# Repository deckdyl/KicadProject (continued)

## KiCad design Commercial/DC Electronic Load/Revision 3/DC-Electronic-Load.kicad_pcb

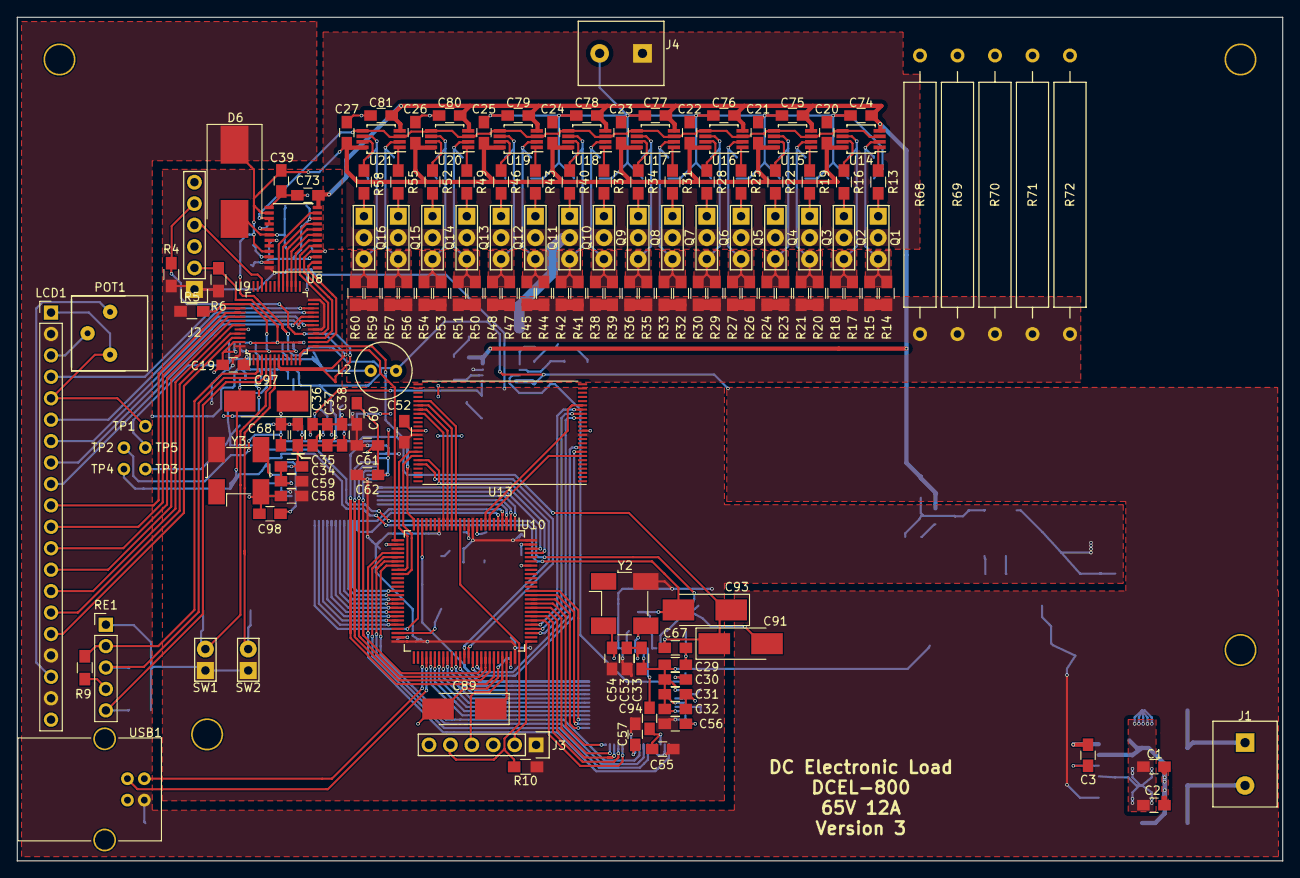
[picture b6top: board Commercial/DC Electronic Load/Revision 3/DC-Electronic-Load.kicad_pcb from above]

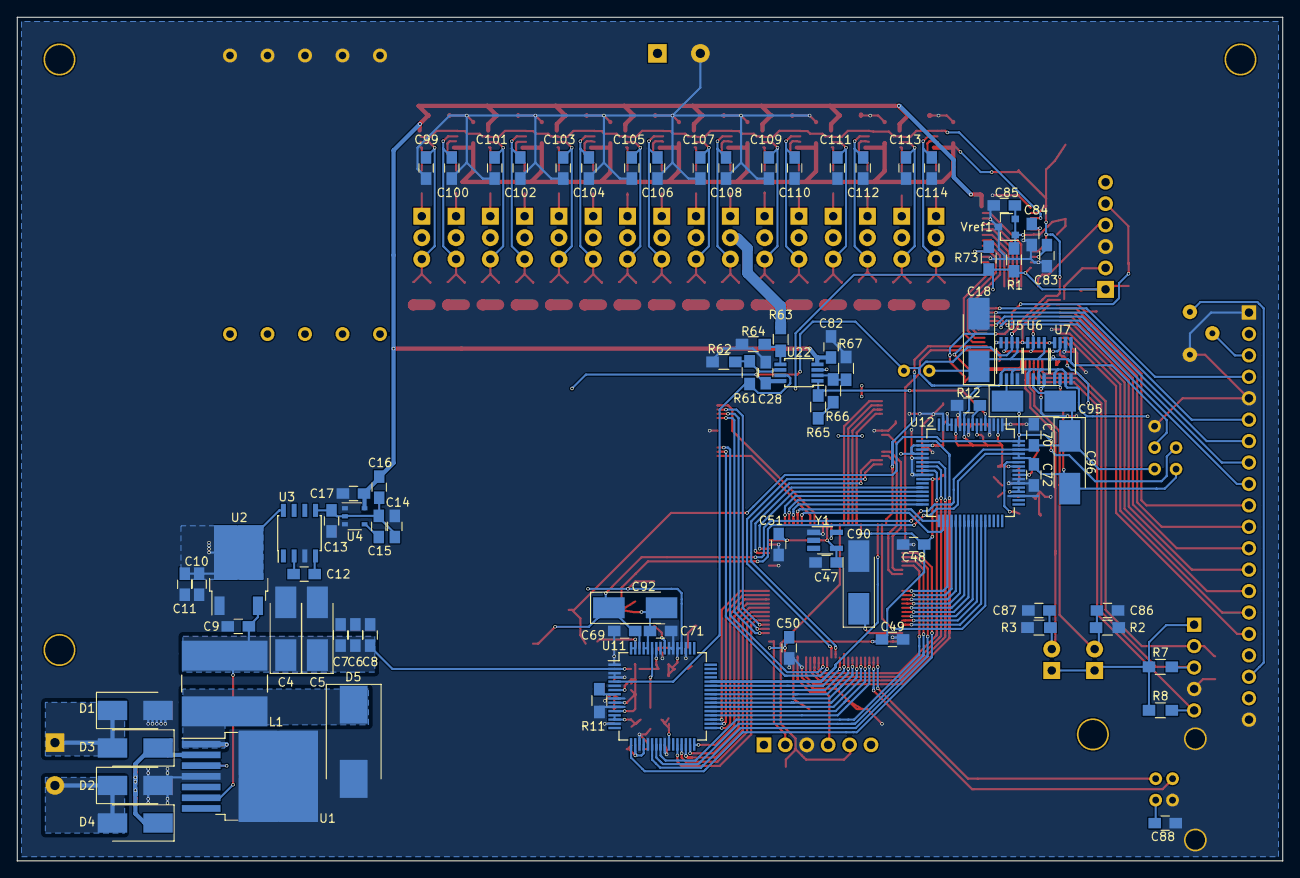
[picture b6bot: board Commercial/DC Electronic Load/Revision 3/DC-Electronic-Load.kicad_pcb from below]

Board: 2 copper layers, 150.0 x 100.0 mm, 241 parts (85 on the bottom side), 181 nets.

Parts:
C1, C2: 22uF; C_0805_HandSoldering
C3, C85, C99, C100, C101, C102, C103, C104, C105, C106, C107, C108, C109, C110, C111, C112, C113, C114: 10nF; C_0805_HandSoldering
C4, C5, C18: 47uF; CP_Tantalum_Case-C_EIA-6032-28_Hand
C6: 4.7uF; C_0805_HandSoldering
C7, C9, C10, C14, C16, C83, C88: 1uF; C_0805_HandSoldering
C8, C11, C15, C17, C19, C20, C21, C22, C23, C24, C25, C26, C27, C28, C29, C30, C31, C32, C33, C34, C35, C36, C37, C38, C39, C47, C48, C49, C50, C51, C52, C53, C54, C55, C56, C57, C58, C59, C60, C61, C62, C67, C68, C69, C70, C71, C72, C73, C74, C75, C76, C77, C78, C79, C80, C81, C82, C86, C87, C94, C98: 100nF; C_0805_HandSoldering
C12, C13: 10uF; C_0805_HandSoldering
C84: 100pF; C_0805_HandSoldering
C89, C90: 2.2uF; CP_Tantalum_Case-C_EIA-6032-28_Hand
C91, C92, C93, C95, C96, C97: 22uF; CP_Tantalum_Case-C_EIA-6032-28_Hand
D1, D2, D3, D4: S2A; D_SMB_Handsoldering
D5, D6: B330; D_SMC_Handsoldering
J1: POWER; Terminal_Block-5mm
J2, J3: ST-Link; Pin_Header_Straight_1x06
J4: Terminal Block; Terminal_Block-5mm
L1: 22uH; Inductor_SMD-9.8X10
L2: 10mH; Inductor_TH-D6.7mm-P3mm
LCD1: LCD_12864; Pin_Header_Straight_1x20_Pitch2.54mm
POT1: 10kΩ; Potentiometer_Bourns_3386
Q1, Q2, Q3, Q4, Q5, Q6, Q7, Q8, Q9, Q10, Q11, Q12, Q13, Q14, Q15, Q16: PSMN5R0-80PS; Pin_Header_Straight_1x03
R1, R13, R16, R19, R22, R25, R28, R31, R34, R37, R40, R43, R46, R49, R52, R55, R58: 100Ω; R_0805_HandSoldering
R2, R3, R4, R10: 10kΩ; R_0805_HandSoldering
R5, R6, R7, R8, R9, R73: 2kΩ; R_0805_HandSoldering
R11, R12: 36kΩ; R_0805_HandSoldering
R14, R15, R17, R18, R20, R21, R23, R24, R26, R27, R29, R30, R32, R33, R35, R36, R38, R39, R41, R42, R44, R45, R47, R48, R50, R51, R53, R54, R56, R57, R59, R60: 2Ω; R_0805_HandSoldering
R61, R62, R64, R65, R66, R67: 26.1kΩ; R_0805_HandSoldering
R63: 750kΩ; R_0805_HandSoldering
R68, R69, R70, R71, R72: 0Ω5; Resistor-5W-PACE05
RE1: Rotary_Encoder; Pin_Header_Straight_1x05_Pitch2.54mm
SW1, SW2: SW_PUSH; Pin_Header_Straight_1x02
TP1, TP2, TP3, TP4, TP5: TEST_1P; Measurement_Point_Round-TH_Small
U1: LM2678-5.0; TO-263-7_TabPin4
U2: NCP1117-3.3; TO-252-2
U3: TC7662; SOIC-8_3.9x4.9mm_Pitch1.27mm
U4: NCP700B-2V8; TSOP-5_1.65x3.05mm_Pitch0.95mm
U5, U6, U7: MAX5215; uMAX
U8: MAX5318; TSSOP-24_4.4x7.8mm_Pitch0.65mm
U9: STM32F373C8T6; LQFP-48_7x7mm_Pitch0.5mm
U10: STM32F446VET6; LQFP-100_14x14mm_Pitch0.5mm
U11, U12: ADS1625/ADS1626; TQFP-64_10x10mm_Pitch0.5mm
U13: TH58BVG3S0; TSOP-I-48_18.4x12mm_Pitch0.5mm
U14, U15, U16, U17, U18, U19, U20, U21, U22: LMP2022; MSOP-8_3x3mm_Pitch0.65mm
USB1: USB_B
Vref1: TL431; SOT-23
Y1: Osc-SMD-SOT23; SOT-23-5_HandSoldering
Y2, Y3: Osc-SMD; Oscillator_SMD_Abracon_ASV-4pin_7.0x5.1mm_HandSoldering

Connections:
12MHz: U10.12, Y1.5
+1V: C71.1, C72.1, C92.2, C93.2, C96.2, C97.2, TP4.1, U7.6, U11.60, U11.61, U12.60, U12.61
+2V5: C69.1, C70.1, C91.2, C92.1, C95.2, C96.1, TP3.1, U6.6, U11.62, U12.62
+3V3: C10.1, C11.1, C47.1, C48.1, C49.1, C50.1, C51.1, C52.1, C53.1, C54.1, C55.1, C56.1, C57.1, C58.1, C59.1, C60.1, C61.1, C62.1, J2.1, J3.1, R1.1, R4.1, R5.1, R6.1, R7.1, R8.1, R10.2, R73.1, RE1.1, SW1.1, SW2.1, U2.2, U3.8, U8.24, U9.17, U9.24, U9.48, U10.11, U10.19, U10.28, U10.50, U10.75, U10.100, U11.13, U11.14, U11.18, U11.20, U11.26, U11.52, U11.53, U12.13, U12.14, U12.18, U12.20, U12.26, U12.52, U12.53, U13.12, U13.37, Y1.4, Y2.4, Y3.4
+4V: C67.1, C68.1, C91.1, C93.1, C95.1, C97.1, TP2.1, U5.6, U11.63, U11.64, U12.63, U12.64
+5V: C4.1, C5.1, C6.1, C7.1, C8.1, C9.1, C20.1, C21.1, C22.1, C23.1, C24.1, C25.1, C26.1, C27.1, C28.1, C29.1, C30.1, C31.1, C32.1, C33.1, C34.1, C35.1, C36.1, C37.1, C38.1, C39.1, C88.1, D6.1, L1.2, L2.1, LCD1.2, LCD1.17, LCD1.19, U1.6, U2.3, U5.2, U5.5, U5.7, U6.5, U6.7, U7.5, U7.7, U8.14, U8.21, U11.2, U11.7, U11.10, U11.12, U11.58, U12.2, U12.7, U12.10, U12.12, U12.58, U14.8, U15.8, U16.8, U17.8, U18.8, U19.8, U20.8, U21.8, U22.8, USB1.1
+5V-REF: C18.1, C19.1, L2.2, TP5.1, U5.1, U6.1, U7.1
-0V5: C16.1, C17.1, C73.2, C74.2, C75.2, C76.2, C77.2, C78.2, C79.2, C80.2, C81.2, C82.2, U4.6, U8.12, U14.4, U15.4, U16.4, U17.4, U18.4, U19.4, U20.4, U21.4, U22.4
-3V3: C13.2, C14.2, C15.2, C16.2, U3.5, U4.2
-5V: LCD1.18, POT1.3
/ADC Data/PC0: U10.15, U13.29
/ADC Data/PC1: U10.16, U13.30
/ADC Data/PC2: U10.17, U13.31
/ADC Data/PC3: U10.18, U13.32
/ADC Data/PC4: U10.33, U13.41
/ADC Data/PC5: U10.34, U13.42
/ADC Data/PC6: U10.63, U13.43
/ADC Data/PC7: U10.64, U13.44
/ADC Data/PD0: U10.81, U11.28
/ADC Data/PD1: U10.82, U11.29
/ADC Data/PD2: U10.83, U11.30
/ADC Data/PD3: U10.84, U11.31
/ADC Data/PD4: U10.85, U11.32
/ADC Data/PD5: U10.86, U11.33
/ADC Data/PD6: U10.87, U11.34
/ADC Data/PD7: U10.88, U11.35
/ADC Data/PD8: U10.55, U11.36
/ADC Data/PD9: U10.56, U11.37
/ADC Data/PD10: U10.57, U11.38
/ADC Data/PD11: U10.58, U11.39
/ADC Data/PD12: U10.59, U11.40
/ADC Data/PD13: U10.60, U11.41
/ADC Data/PD14: U10.61, U11.42
/ADC Data/PD15: U10.62, U11.43
/ADC Data/PE0: U10.97, U12.28
/ADC Data/PE1: U10.98, U12.29
/ADC Data/PE2: U10.1, U12.30
/ADC Data/PE3: U10.2, U12.31
/ADC Data/PE4: U10.3, U12.32
/ADC Data/PE5: U10.4, U12.33
/ADC Data/PE6: U10.5, U12.34
/ADC Data/PE7: U10.38, U12.35
/ADC Data/PE8: U10.39, U12.36
/ADC Data/PE9: U10.40, U12.37
/ADC Data/PE10: U10.41, U12.38
/ADC Data/PE11: U10.42, U12.39
/ADC Data/PE12: U10.43, U12.40
/ADC Data/PE13: U10.44, U12.41
/ADC Data/PE14: U10.45, U12.42
/ADC Data/PE15: U10.46, U12.43
/ADC Data/USB_DM: U10.53, USB1.2
/ADC Data/USB_DP: U10.54, USB1.3
DAC_Busy: R73.2, U8.4, U9.15
DAC_CS: U8.9, U9.29
DAC_Disable: U8.11, U9.30
DAC_LDAC: U8.5, U9.16
DAC_MISO: U8.6, U9.26
DAC_MOSI: U8.7, U9.27
DAC_OUT: U8.15, U8.16, U14.3, U14.5, U15.3, U15.5, U16.3, U16.5, U17.3, U17.5, U18.3, U18.5, U19.3, U19.5, U20.3, U20.5, U21.3, U21.5
DAC_Ready: U8.2, U9.14
DAC_SCK: U8.8, U9.28
F3NRST: J2.5, R4.2, U9.7
F3SWDCLK: J2.2, R6.2, U5.4, U6.4, U7.4, U9.37
F3SWDIO: J2.4, U9.34
F4NRST: J3.5, R10.1, U10.14
F4SWDCLK: J3.2, U10.76
F4SWDIO: J3.4, U10.72
FLASH_ALE: U10.79, U13.17
FLASH_CLE: U10.78, U13.16
FLASH_R/~B~: U10.7, U13.7
FLASH_~CE~: U10.66, U13.9
FLASH_~RE~: U10.65, U13.8
FLASH_~WE~: U10.80, U13.18
FLASH_~WP~: U10.8, U13.19
GND: C1.2, C2.2, C4.2, C5.2, C6.2, C7.2, C8.2, C9.2, C10.2, C11.2, C13.1, C14.1, C17.2, C18.2, C19.2, C20.2, C21.2, C22.2, C23.2, C24.2, C25.2, C26.2, C27.2, C28.2, C29.2, C30.2, C31.2, C32.2, C33.2, C34.2, C35.2, C36.2, C37.2, C38.2, C39.2, C47.2, C48.2, C49.2, C50.2, C51.2, C52.2, C53.2, C54.2, C55.2, C56.2, C57.2, C58.2, C59.2, C60.2, C61.2, C62.2, C67.2, C68.2, C69.2, C70.2, C71.2, C72.2, C73.1, C74.1, C75.1, C76.1, C77.1, C78.1, C79.1, C80.1, C81.1, C82.1, C83.2, C84.2, C85.2, C86.2, C87.2, C88.2, C89.2, C90.2, C94.2, C98.2, C99.2, C100.2, C101.2, C102.2, C103.2, C104.2, C105.2, C106.2, C107.2, C108.2, C109.2, C110.2, C111.2, C112.2, C113.2, C114.2, D1.2, D3.2, D5.2, J2.3, J3.3, J4.2, LCD1.1, LCD1.5, LCD1.20, POT1.1, R2.2, R3.2, R9.2, R11.2, R12.2, R62.2, R64.2, R67.2, R68.2, R69.2, R70.2, R71.2, R72.2, RE1.4, TP1.1, U1.4, U2.1, U3.3, U4.1, U4.3, U5.8, U6.8, U7.2, U7.8, U8.3, U8.10, U8.13, U8.19, U8.20, U8.23, U9.44, U9.47, U10.10, U10.27, U10.49, U10.74, U10.94, U10.99, U11.1, U11.3, U11.4, U11.6, U11.9, U11.11, U11.15, U11.19, U11.21, U11.25, U11.51, U11.54, U11.55, U11.57, U12.1, U12.3, U12.4, U12.6, U12.9, U12.11, U12.15, U12.19, U12.21, U12.25, U12.51, U12.54, U12.55, U12.57, U13.13, U13.36, USB1.4, USB1.5, Vref1.3, Y1.1, Y2.2, Y3.2
I2C_REFV_SCL: R5.2, U5.3, U6.3, U7.3, U9.38
IADC: R65.1, U12.5, U22.1
I_OTR: U10.68, U12.23
I_SIGN: U10.24, U12.44
I_Sense: R14.2, R15.2, R17.2, R18.2, R20.2, R21.2, R23.2, R24.2, R26.2, R27.2, R29.2, R30.2, R32.2, R33.2, R35.2, R36.2, R38.2, R39.2, R41.2, R42.2, R44.2, R45.2, R47.2, R48.2, R50.2, R51.2, R53.2, R54.2, R56.2, R57.2, R59.2, R60.2, R68.1, R69.1, R70.1, R71.1, R72.1, U22.3
I_~PD~: U10.70, U12.17
I_~RD~: U10.69, U12.22
LCD_EN: LCD1.6, U9.21
LCD_RS: LCD1.4, U9.22
LOAD_IN: J4.1, Q1.2, Q2.2, Q3.2, Q4.2, Q5.2, Q6.2, Q7.2, Q8.2, Q9.2, Q10.2, Q11.2, Q12.2, Q13.2, Q14.2, Q15.2, Q16.2, R63.1
LOAD_V: R61.1, U11.5, U22.7
unnamed: C1.1, C2.1, D2.1, D4.1, U1.2
unnamed: C3.1, D5.1, L1.1, U1.1
unnamed: C3.2, U1.3
unnamed: C12.1, U3.2
unnamed: C12.2, U3.4
unnamed: C15.1, U4.4
unnamed: C83.1, U8.22
unnamed: C84.1, U8.17
unnamed: C85.1, D6.2, R1.2, U8.18, Vref1.1, Vref1.2
unnamed: C89.1, U10.73
unnamed: C90.1, U10.48
unnamed: C94.1, U11.59
unnamed: C98.1, U12.59
unnamed: C99.1, Q1.3, R14.1, R15.1, U14.2
unnamed: C100.1, Q2.3, R17.1, R18.1, U14.6
unnamed: C101.1, Q3.3, R20.1, R21.1, U15.2
unnamed: C102.1, Q4.3, R23.1, R24.1, U15.6
unnamed: C103.1, Q5.3, R26.1, R27.1, U16.2
unnamed: C104.1, Q6.3, R29.1, R30.1, U16.6
unnamed: C105.1, Q7.3, R32.1, R33.1, U17.2
unnamed: C106.1, Q8.3, R35.1, R36.1, U17.6
unnamed: C107.1, Q9.3, R38.1, R39.1, U18.2
unnamed: C108.1, Q10.3, R41.1, R42.1, U18.6
unnamed: C109.1, Q11.3, R44.1, R45.1, U19.2
unnamed: C110.1, Q12.3, R47.1, R48.1, U19.6
unnamed: C111.1, Q13.3, R50.1, R51.1, U20.2
unnamed: C112.1, Q14.3, R53.1, R54.1, U20.6
unnamed: C113.1, Q15.3, R56.1, R57.1, U21.2
unnamed: C114.1, Q16.3, R59.1, R60.1, U21.6
unnamed: D1.1, D2.2, J1.1
unnamed: D3.1, D4.2, J1.2
unnamed: LCD1.3, POT1.2
unnamed: LCD1.7, U9.18
unnamed: LCD1.8, U9.19
unnamed: LCD1.9, U9.20
unnamed: LCD1.10, U9.39
unnamed: LCD1.11, U9.40
unnamed: LCD1.12, U9.41
unnamed: LCD1.13, U9.42
unnamed: LCD1.14, U9.43
unnamed: LCD1.15, U9.45
unnamed: LCD1.16, U9.46
unnamed: Q1.1, R13.1
unnamed: Q2.1, R16.1
unnamed: Q3.1, R19.1
unnamed: Q4.1, R22.1
unnamed: Q5.1, R25.1
unnamed: Q6.1, R28.1
unnamed: Q7.1, R31.1
unnamed: Q8.1, R34.1
unnamed: Q9.1, R37.1
unnamed: Q10.1, R40.1
unnamed: Q11.1, R43.1
unnamed: Q12.1, R46.1
unnamed: Q13.1, R49.1
unnamed: Q14.1, R52.1
unnamed: Q15.1, R55.1
unnamed: Q16.1, R58.1
unnamed: R11.1, U11.8
unnamed: R12.1, U12.8
unnamed: R13.2, U14.1
unnamed: R16.2, U14.7
unnamed: R19.2, U15.1
unnamed: R22.2, U15.7
unnamed: R25.2, U16.1
unnamed: R28.2, U16.7
unnamed: R31.2, U17.1
unnamed: R34.2, U17.7
unnamed: R37.2, U18.1
unnamed: R40.2, U18.7
unnamed: R43.2, U19.1
unnamed: R46.2, U19.7
unnamed: R49.2, U20.1
unnamed: R52.2, U20.7
unnamed: R55.2, U21.1
unnamed: R58.2, U21.7
unnamed: R61.2, R62.1, U22.6
unnamed: R63.2, R64.1, U22.5
unnamed: R65.2, R66.1
unnamed: R66.2, R67.1, U22.2
unnamed: U11.56, Y2.3
unnamed: U12.56, Y3.3
RE1: R7.2, RE1.3, U9.3
RE2: R8.2, RE1.5, U9.4
RESW: R9.1, RE1.2, U9.2
SW_LEFT: C86.1, R2.1, SW1.2, U9.5
SW_RIGHT: C87.1, R3.1, SW2.2, U9.6
USART_TOF3: U9.13, U10.25
USART_TOF4: U9.12, U10.26
V_OTR: U10.31, U11.23
V_SIGN: U10.23, U11.44
V_~PD~: U10.29, U11.17
V_~RD~: U10.30, U11.22
~I_READY~: U10.67, U12.24
~V_READY~: U10.32, U11.24

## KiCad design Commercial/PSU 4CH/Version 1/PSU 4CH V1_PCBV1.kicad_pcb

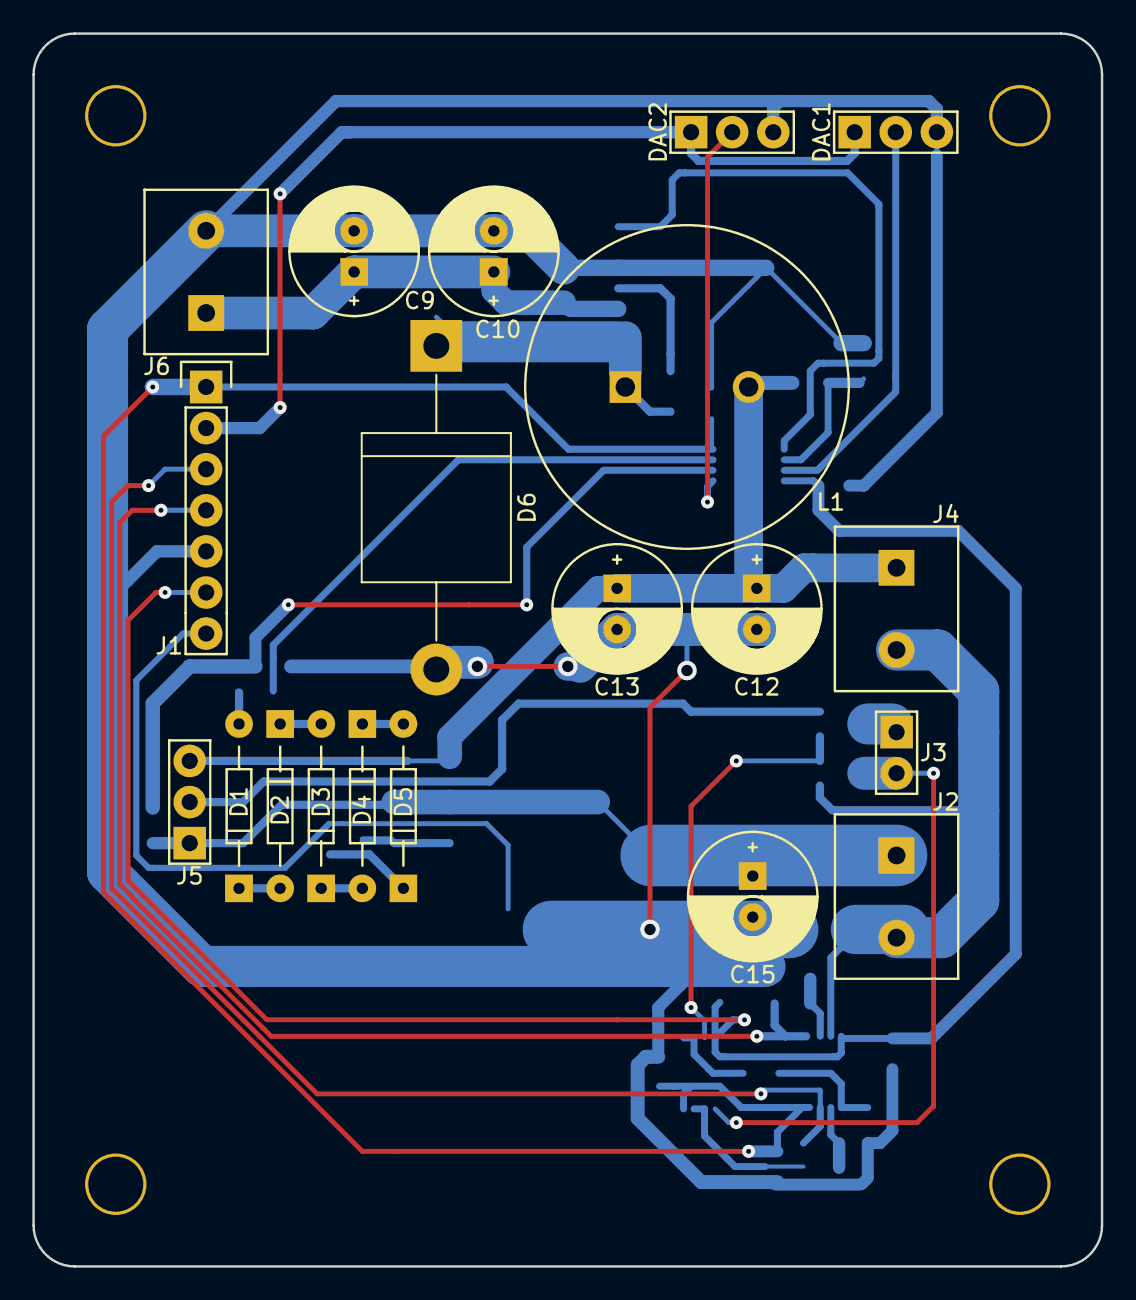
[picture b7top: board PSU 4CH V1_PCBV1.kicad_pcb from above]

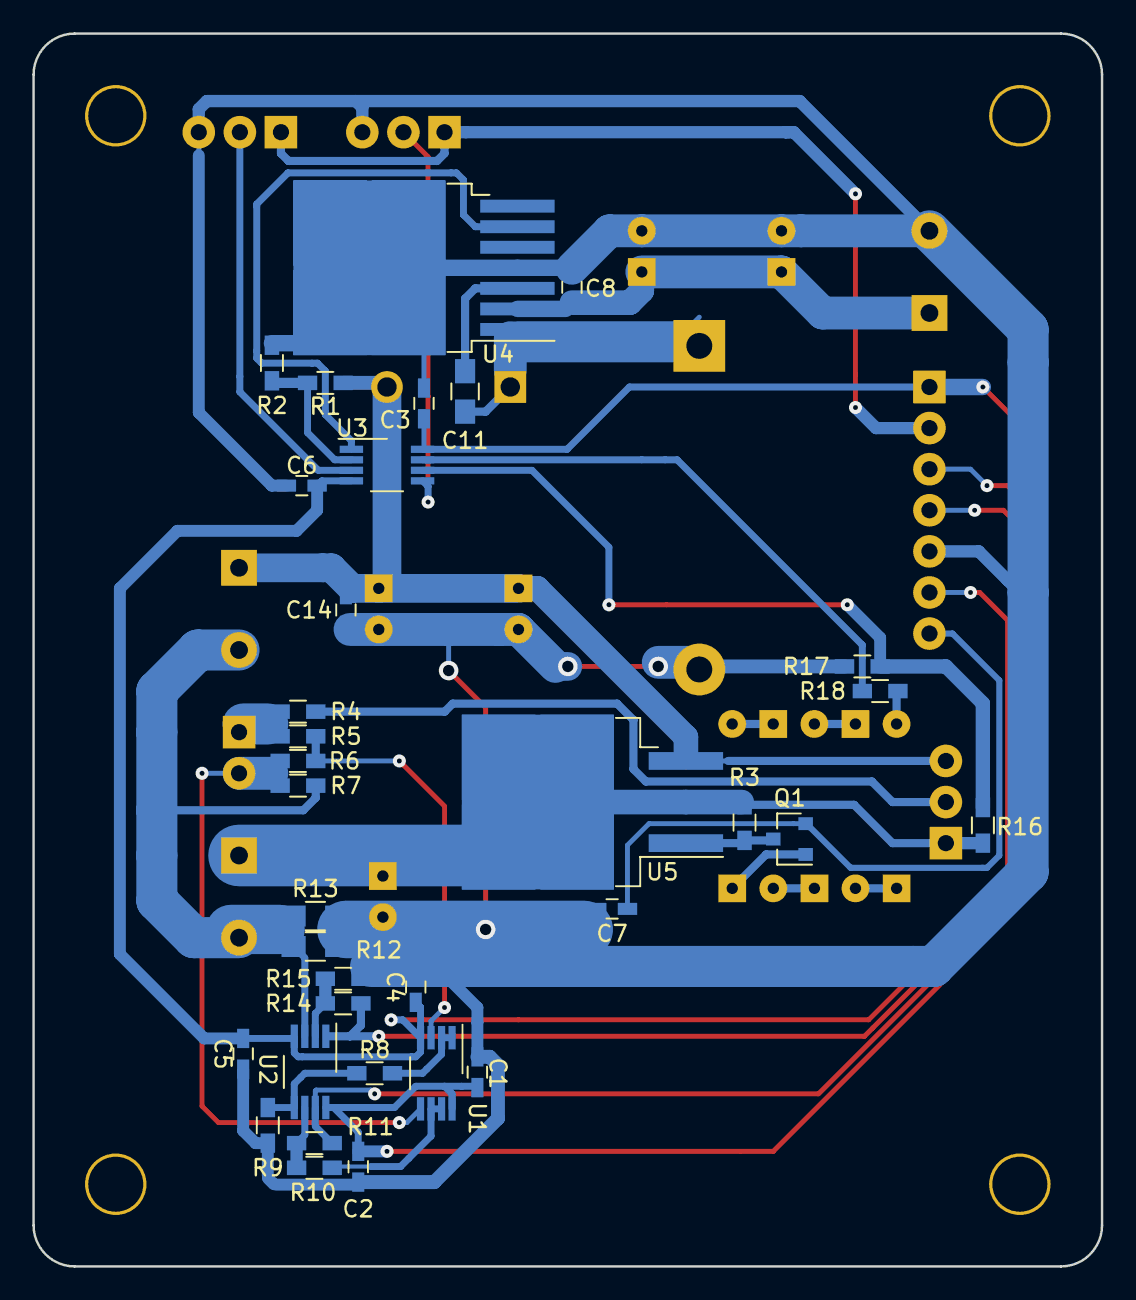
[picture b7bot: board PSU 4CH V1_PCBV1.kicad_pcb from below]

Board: 2 copper layers, 66.0 x 76.2 mm, 54 parts (34 on the bottom side), 35 nets.

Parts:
C1, C2, C3, C4, C5, C6, C7, C8, C14: 470nF; C_0603_HandSoldering
C9, C10, C12, C13, C15: 22uF; Cap_Pol_Radial_D8_P2
C11: 10nF; C_0805_HandSoldering
D1, D2, D3, D4, D5: 1N914; 1N4148
D6: 15SQ045; D_P600_R-6_P20.00mm_Horizontal
DAC1: BUCK_DAC; Pin_Header_Straight_1x03
DAC2: LINEAR DAC; Pin_Header_Straight_1x03
J1: MCU I/O; Pin_Header_Straight_1x07
J2, J4: PSU Out; Terminal_Block-5mm
J3: PSU FB; Pin_Header_Straight_1x02
J5: Select; Pin_Header_Straight_1x03
J6: Input; Terminal_Block-5mm
L1: 22uH; Inductor-22uH-5.4A
Q1: FJV1845; SOT-23
R1, R5, R16: 91kΩ; R_0603_HandSoldering
R2, R6, R17: 10kΩ; R_0603_HandSoldering
R3: 680Ω; R_0603_HandSoldering
R4, R7: 10Ω; R_0603_HandSoldering
R8, R9, R10, R11, R15: 1kΩ; R_0603_HandSoldering
R12, R13: 12mΩ; R_0805_HandSoldering
R14: 100kΩ; R_0603_HandSoldering
R18: 75kΩ; R_0603_HandSoldering
U1, U2, U3: LMP2022; VSSOP-8_3.0x3.0mm_Pitch0.65mm
U4: LM2678SX-ADJ; TO-263-7_TabPin4
U5: LMS1585A; TO-263-3_TabPin2

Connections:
+3V3: DAC1.1, DAC2.1, J1.2
+5V: C1.1, C2.1, C3.1, J1.1, U1.8, U2.8, U3.8
-0V5: C4.2, C5.2, C6.2, J1.6, U1.4, U2.4, U3.4
-2V8: C7.2, J1.7, Q1.2
/DAC_BUCK: DAC1.2, U3.3
/DAC_LINEAR: DAC2.2, U3.5
/I-ADC: J1.4, R14.1, U2.1
/Input-V+: C8.1, C9.1, C10.1, J6.1, U4.2
/Output-Buck: C12.1, C13.1, C14.1, J4.1, J5.3, L1.2, R1.1, U5.3
/Output-GND: J2.2, J4.2, R7.2, R12.1, R13.1, U2.3
/Output-Linear: C15.1, J2.1, J5.1, R3.1, R16.1, U5.2
/V-ADC: J1.3, R11.1, U2.7
/Vfb+: J3.1, R4.2, R5.1
/Vfb-: J3.2, R6.2, R7.1, U1.5
/Vfb-Buck: U3.1, U4.6
/Vfb-Linear: Q1.3, R3.2, U5.1
GND: C1.2, C2.2, C3.2, C4.1, C5.1, C6.1, C7.1, C8.2, C9.2, C10.2, C12.2, C13.2, C14.2, C15.2, D6.2, DAC1.3, DAC2.3, J1.5, J6.2, R2.2, R9.2, R12.2, R13.2, R15.2, R17.2, U4.4
unnamed: C11.1, D6.1, L1.1, U4.1
unnamed: C11.2, U4.3
unnamed: D1.1, D2.2
unnamed: D1.2, R18.1
unnamed: D2.1, D3.2
unnamed: D3.1, D4.2
unnamed: D4.1, D5.2
unnamed: D5.1, Q1.1
unnamed: J5.2, R4.1
unnamed: R1.2, R2.1, U3.2
unnamed: R5.2, R6.1, U1.3
unnamed: R8.1, R9.1, U2.5
unnamed: R8.2, U1.1, U1.2
unnamed: R10.1, R11.2, U2.6
unnamed: R10.2, U1.6, U1.7
unnamed: R14.2, R15.1, U2.2
unnamed: R16.2, R17.1, U3.6
unnamed: R18.2, U3.7
